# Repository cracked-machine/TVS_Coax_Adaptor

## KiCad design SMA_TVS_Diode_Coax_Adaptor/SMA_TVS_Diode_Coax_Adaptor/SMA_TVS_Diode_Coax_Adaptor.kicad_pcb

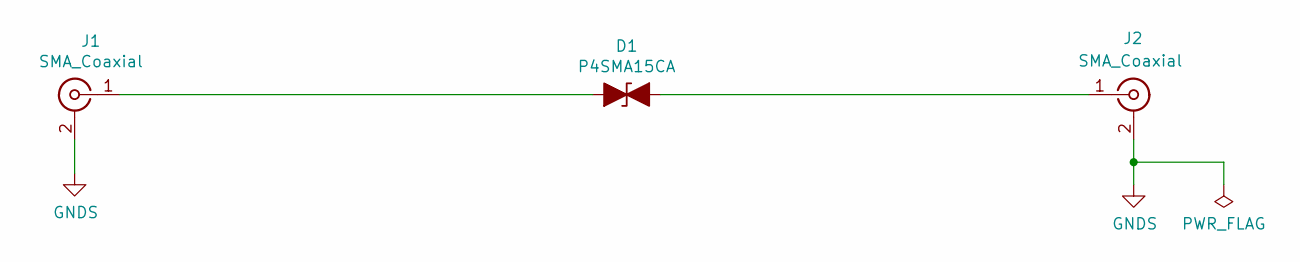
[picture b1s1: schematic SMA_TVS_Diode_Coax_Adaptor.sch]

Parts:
D1: P4SMA15CA; D_SMA_Handsoldering
J1, J2: SMA_Coaxial; SMA_Amphenol_901-144_Vertical

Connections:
GNDS: J1.2 (Ext), J2.2 (Ext)
unnamed: D1.1 (A1), J1.1 (In)
unnamed: D1.2 (A2), J2.1 (In)

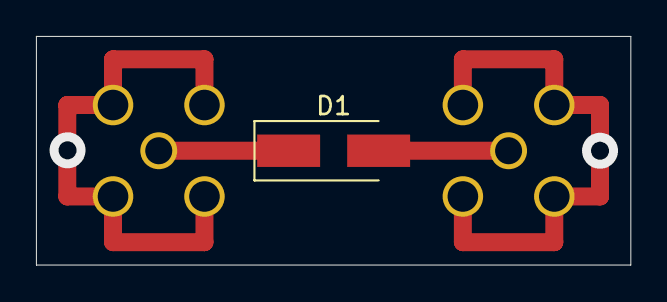
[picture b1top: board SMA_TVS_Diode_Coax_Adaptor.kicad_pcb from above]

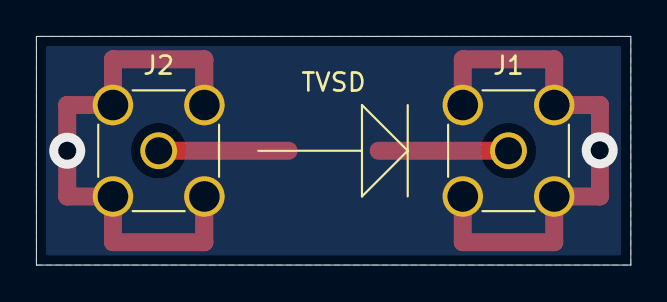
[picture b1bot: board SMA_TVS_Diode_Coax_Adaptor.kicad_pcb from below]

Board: 2 copper layers, 33.0 x 12.7 mm, 3 parts (2 on the bottom side), 3 nets.

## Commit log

2020-05-26 created "SMA_TVS_Diode_Coax_Adaptor"
